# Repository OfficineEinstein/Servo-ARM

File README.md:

# Servo-ARM
Tester Controller per servo analogici (Futaba)
## Descrizione di massima
Questo dispoositivo nasce per consentire l'agevole studio dei generatori PWM, delle loro funzionalità e del loro sfruttamento. Per praticità è stato individuato come controllore per servo meccanismi a tre fili di tipo Futaba ma, in effetti è utilizzabile per un'ampio spettro di esperienze che comprendono l'utilizzo di segnali PWM o comunque la generazione di onde quadre o treni di impulsi anche associati ad un'uscita di potenza.

Il dispositivo si basa su 
##### * un microcontrollore Atmel ATMEGA328P installato su una scheda Arduino Nano equivalente.
##### * tre potenziometri per la scelta dell'ampiezza dell'inpulso dei 3 generatori PWM.
##### * quattro uscite per servo controllate tramite quattro semi ponti H.
##### * un alimentatore con ingresso in corrente continua o alternata e due unità di uscita separate (logica e servo).
Il potenziometro numero 3 è collegato a due uscite così da poter controllare due servo in contemporanea.

# Hardware
## r00
La versione zero (quella di cui attualmente sono disponibili i PCB) presenta alcune criticità in fase di correzione nella versione r01

### Ponnte raddrizzatore
Il ponte previsto nel PCB ha una piedinatura inusuale per cui, se si usa un ponte standard si devono piegare ed incrociare i piedini in maniera da posizion arli correttamente

### Piedinatura di uscita
La piedinatura di uscita per i servo ha i piedini 2 e 3 invertiti (fa riferimento ad un tipo di servo diverso dallo standard Futaba)

## r01
Nella versione r01 attualmente in fase di perfezionamento tutti i problemi evidenziati nella versione r00 sono in fase di eliminazione. I PCB della versione saranno facilemente riconoscibili anche attraverso la dicitura PCB r01 riportata nelle serigrafie

# Software
Al momento non è stata rilasciata una versione di riferimento del codice per il funzionamento di questo strumento.

Si ricorda che se si adotta come microcontrollore la scheda Maker Nano, in fase di compilazione si dovrà scegliere la versione di bootloader più aggiornata diversamente verrà restituito un errore in fase di caricamento del codice.

Il dispositivo si basa sulla funzione PWM disponibile nella libreria di base di Arduino (analogWrite()).
Anche se in fase di sperimentazione è possibile utilizzare le librerie disponibili per il controllo dei servo, sarebbe opportuno controllare i generatori PWM direttamente ovvero tramite comandi analogWrite() e non tramite chiamate alle librerie per il controllo dei servo.

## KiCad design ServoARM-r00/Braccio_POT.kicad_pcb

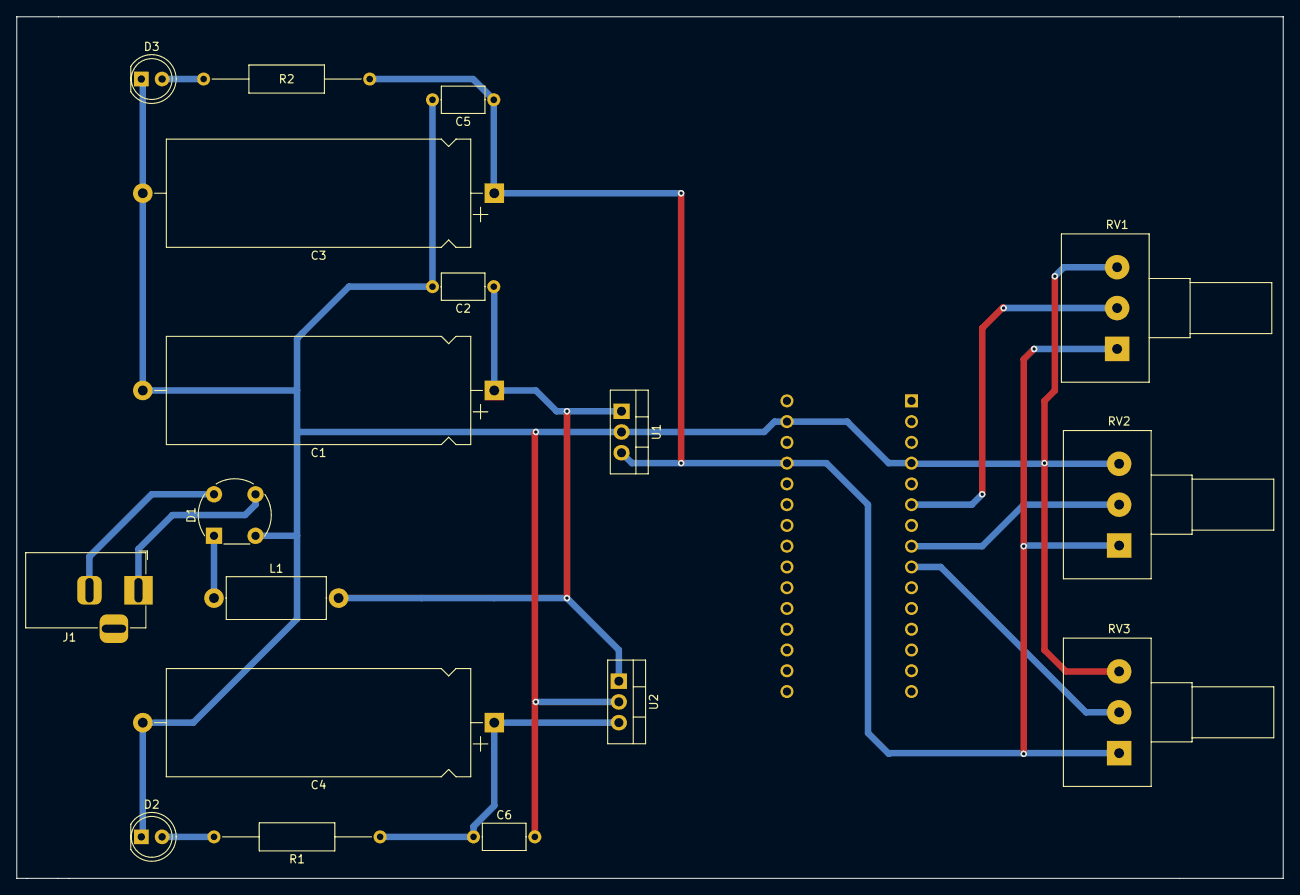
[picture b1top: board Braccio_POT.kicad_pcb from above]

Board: 2 copper layers, 154.9 x 105.4 mm, 19 parts (1 on the bottom side), 12 nets.

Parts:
A1: Arduino_Nano_v3.x; Arduino_Nano
C1, C3, C4: C_Polarized; CP_Axial_L37.0mm_D13.0mm_P43.00mm_Horizontal
C2, C5, C6: C; C_Axial_L5.1mm_D3.1mm_P7.50mm_Horizontal
D1: D_Bridge_+-AA; Diode_Bridge_Round_D8.9mm
D2: LED Verde; LED_D5.0mm
D3: LED Rosso; LED_D5.0mm
J1: Barrel_Jack_MountingPin; BarrelJack_Horizontal
L1: L; L_Axial_L12.0mm_D5.0mm_P15.24mm_Horizontal_Fastron_MISC
R1, R2: R; R_Axial_DIN0309_L9.0mm_D3.2mm_P20.32mm_Horizontal
RV1, RV2, RV3: R_Potentiometer; Potentiometer_Alps_RK163_Single_Horizontal
U1, U2: LM7805_TO220; TO-220-3_Vertical

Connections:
/Unità Alimentazione/5V-CPU: A1.27 (+5V), C3.1, C5.1, R2.1, RV1.1, RV2.1, RV3.1, U1.3 (VO)
/Unità Alimentazione/5V-SERVO: C4.1, C6.1, R1.1, U2.3 (VO)
/Unità Alimentazione/GND-Pow: A1.4 (GND), A1.29 (GND), C1.2, C2.2, C3.2, C4.2, C5.2, C6.2, D1.2 (-), D2.1 (K), D3.1 (K), RV1.3, RV2.3, RV3.3, U1.2 (GND), U2.2 (GND)
/Unità CPU/Pot1: A1.6 (D3), RV1.2
/Unità CPU/Pot2: A1.8 (D5), RV2.2
/Unità CPU/Pot3: A1.9 (D6), RV3.2
unnamed: C1.1, C2.1, L1.2, U1.1 (VI), U2.1 (VI)
unnamed: D1.1 (+), L1.1
unnamed: D1.3, J1.1
unnamed: D1.4, J1.2
unnamed: D2.2 (A), R1.2
unnamed: D3.2 (A), R2.2

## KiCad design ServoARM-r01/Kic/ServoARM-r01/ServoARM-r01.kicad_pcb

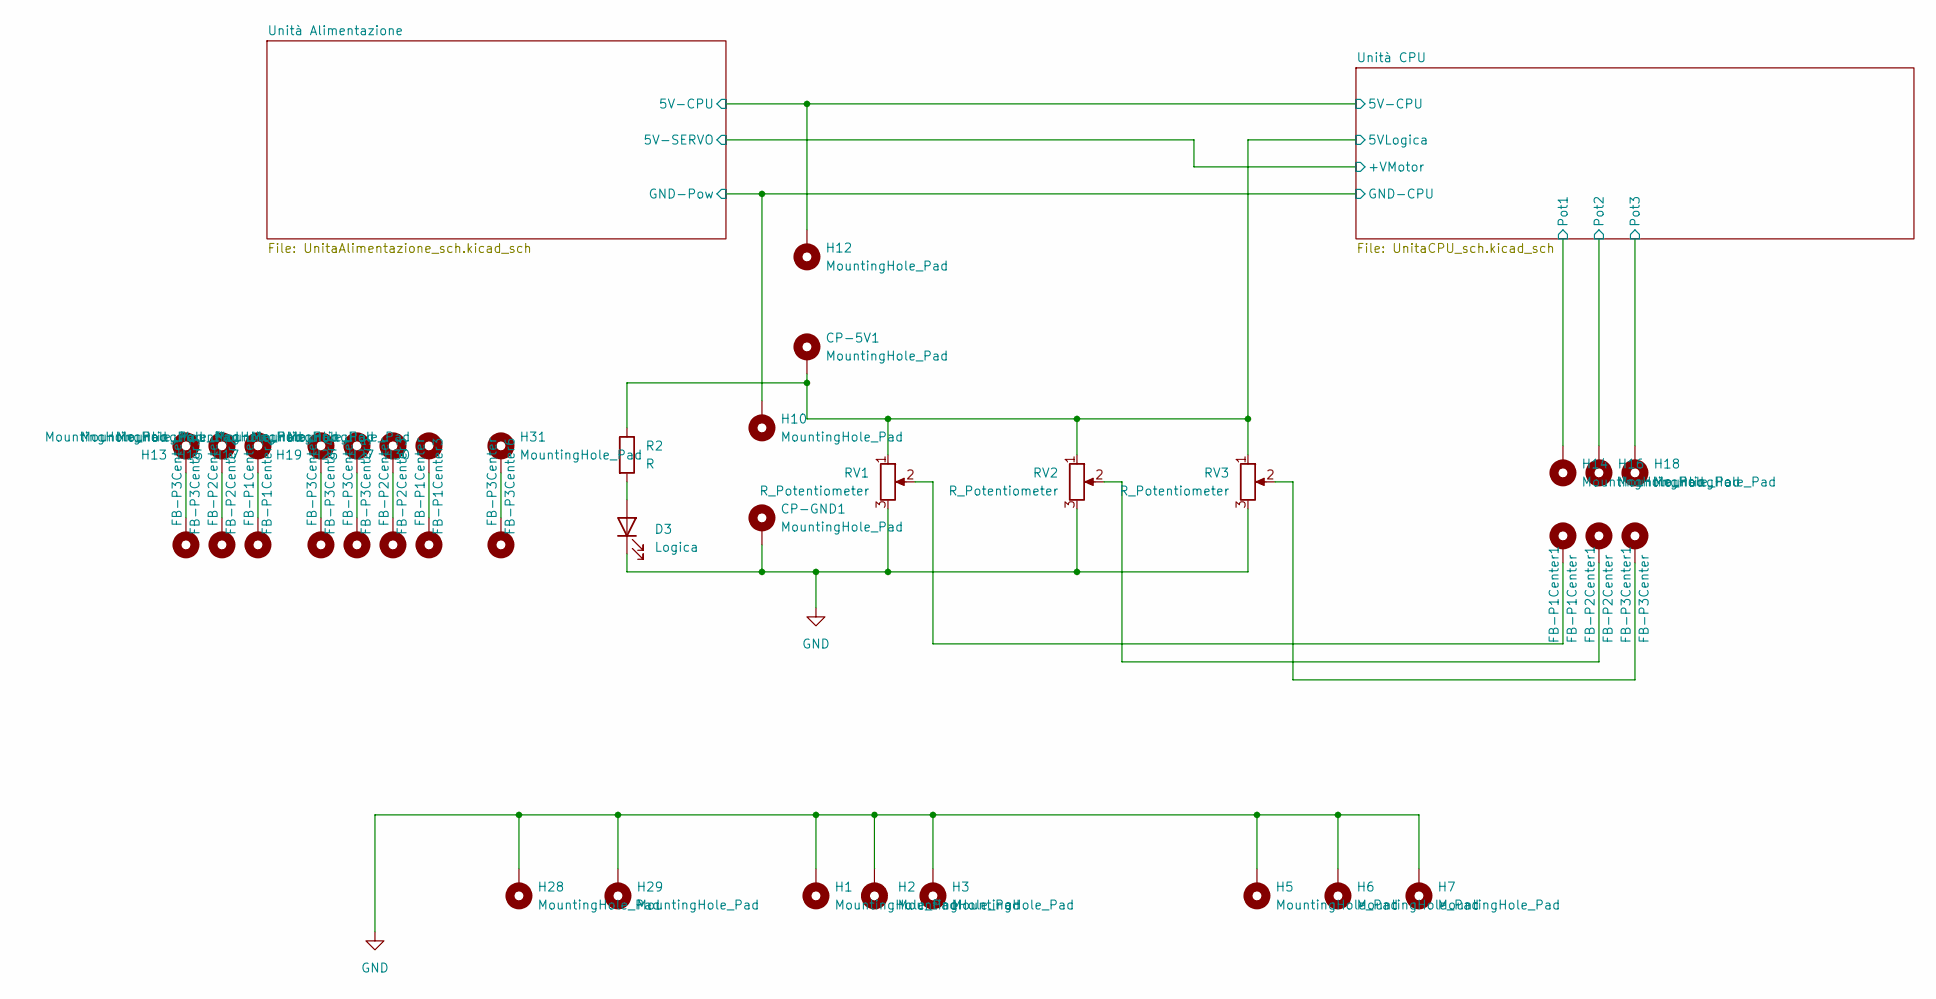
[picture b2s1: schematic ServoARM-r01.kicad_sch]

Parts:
CP-5V1: MountingHole_Pad; Asola
CP-GND1: MountingHole_Pad; Asola
D3: Logica; LED_D5.0mm
FB-P1Center1: FB-P1Center; Asola
FB-P1Center2, FB-P1Center3: FB-P1Center; TenonePerAsola
FB-P2Center1: FB-P2Center; Asola
FB-P2Center2, FB-P2Center3: FB-P2Center; TenonePerAsola
FB-P3Center1: FB-P3Center; Asola
FB-P3Center3, FB-P3Center4, FB-P3Center5, FB-P3Center6: FB-P3Center; TenonePerAsola
H1, H2: MountingHole_Pad; MountingHole_4.3x6.2mm_M4_Pad_Via
H3: MountingHole_Pad; MountingHole_4.3mm_M4_Pad_Via
H5, H6, H7, H28, H29: MountingHole_Pad; MountingHole_6.5mm_Pad_Via
H10, H12, H14, H16, H18: MountingHole_Pad; Asola
H13, H15, H17, H19, H25, H27, H30, H31: MountingHole_Pad; TenonePerAsola
R2: R; R_Axial_DIN0309_L9.0mm_D3.2mm_P20.32mm_Horizontal
RV1, RV2, RV3: R_Potentiometer; Potentiometer_Omeg_PC16BU_Vertical

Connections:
/Unità Alimentazione/5V-CPU: H12.1; also elsewhere on the board
/Unità CPU/5VLogica: CP-5V1.1, R2.1, RV1.1, RV2.1, RV3.1; also elsewhere on the board
/Unità CPU/Pot1: H14.1; also elsewhere on the board
/Unità CPU/Pot2: H16.1; also elsewhere on the board
/Unità CPU/Pot3: H18.1; also elsewhere on the board
GND: CP-GND1.1, D3.1 (K), H1.1, H2.1, H3.1, H5.1, H6.1, H7.1, H10.1, H28.1, H29.1, RV1.3, RV2.3, RV3.3; also elsewhere on the board
unnamed: D3.2 (A), R2.2
unnamed: FB-P1Center1.1, RV1.2
unnamed: FB-P1Center2.1, H17.1
unnamed: FB-P1Center3.1, H30.1
unnamed: FB-P2Center1.1, RV2.2
unnamed: FB-P2Center2.1, H15.1
unnamed: FB-P2Center3.1, H27.1
unnamed: FB-P3Center1.1, RV3.2
unnamed: FB-P3Center3.1, H13.1
unnamed: FB-P3Center4.1, H19.1
unnamed: FB-P3Center5.1, H25.1
unnamed: FB-P3Center6.1, H31.1

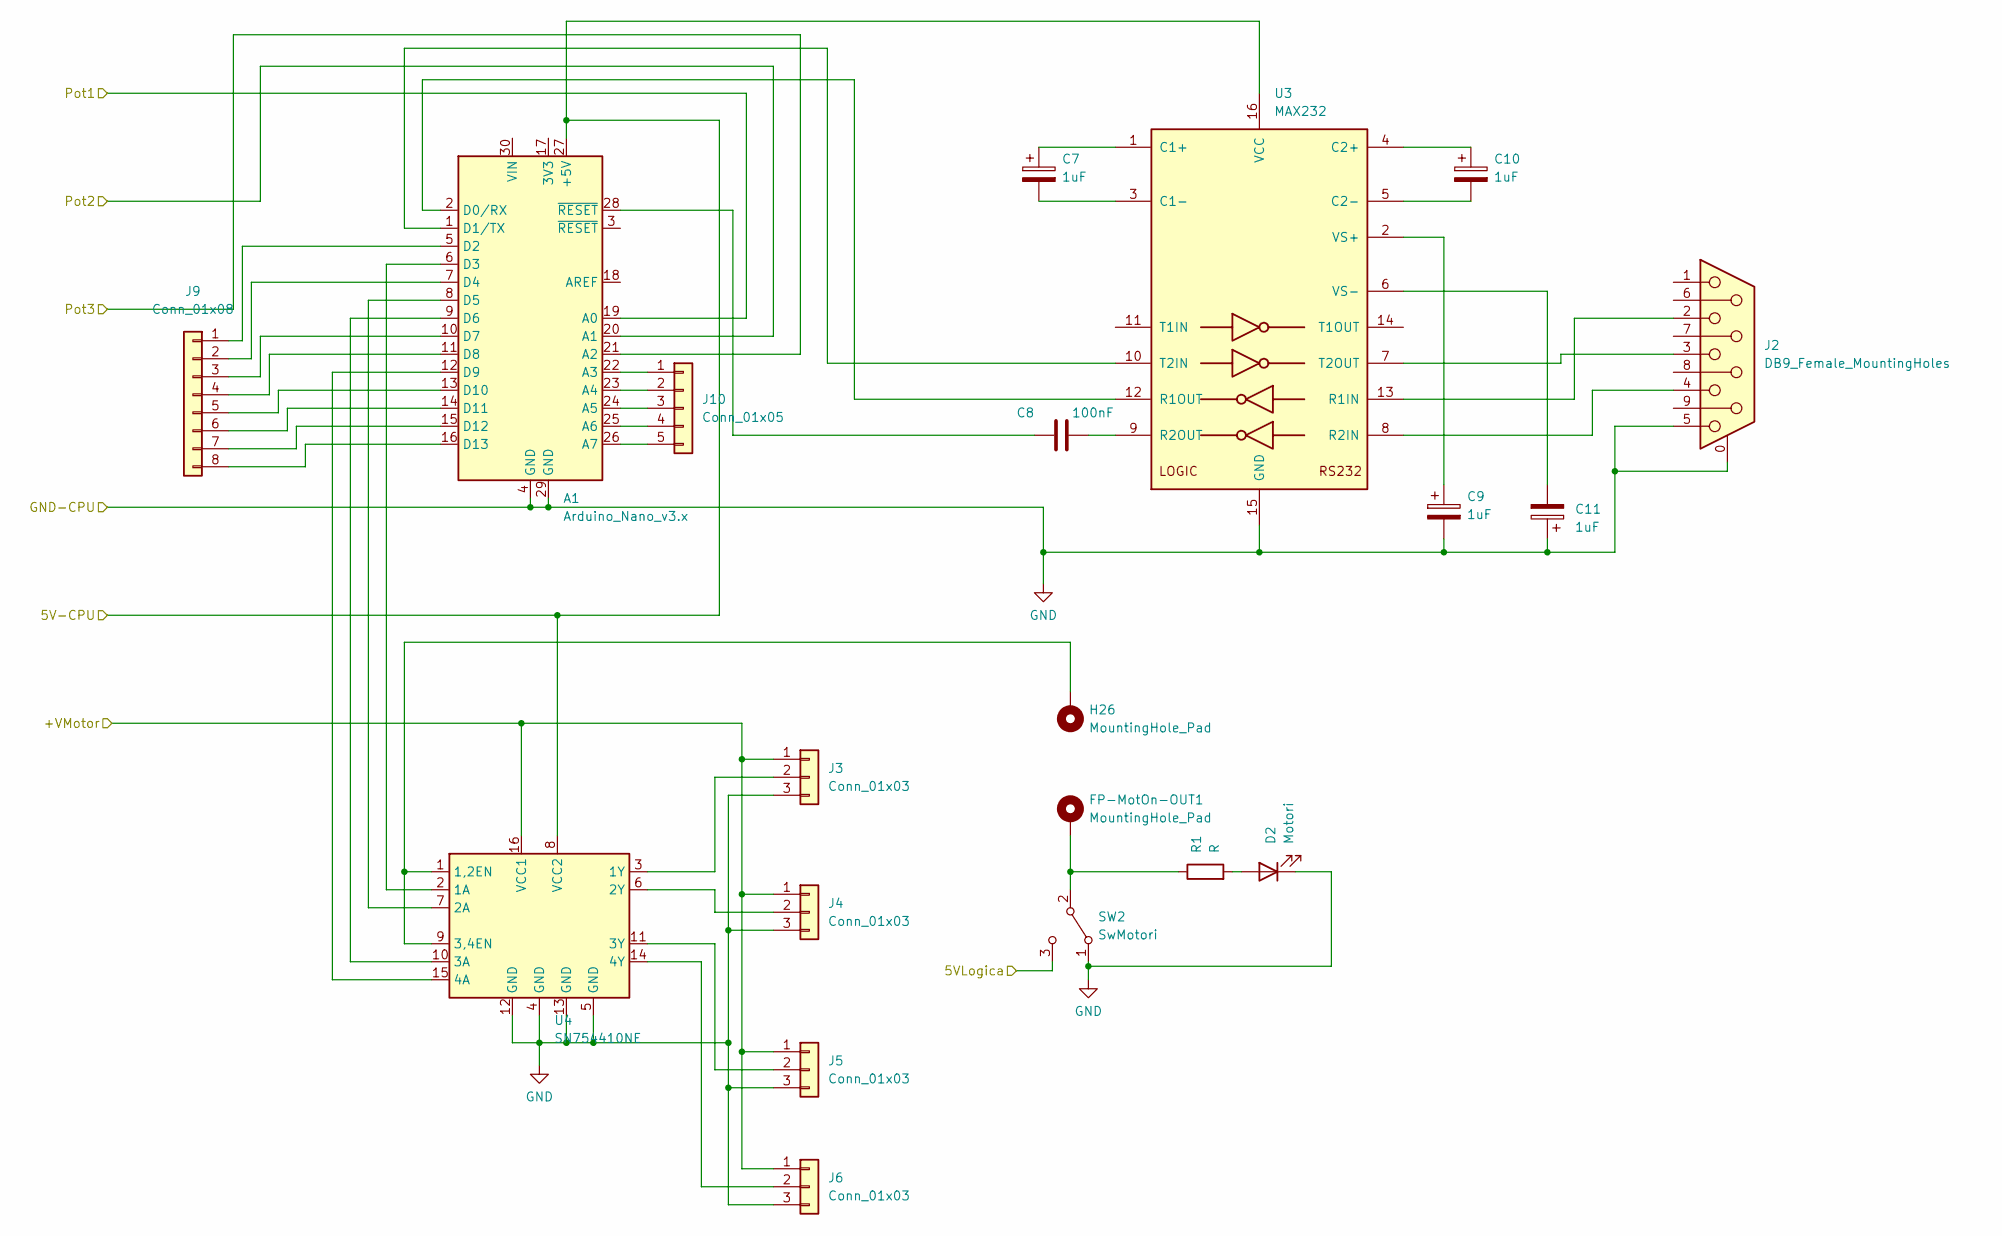
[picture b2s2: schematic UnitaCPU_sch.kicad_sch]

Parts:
A1: Arduino_Nano_v3.x; Arduino_Nano
C7, C9, C10, C11: 1uF; CP_Radial_D4.0mm_P2.00mm
C8: 100nF; C_Axial_L5.1mm_D3.1mm_P7.50mm_Horizontal
D2: Motori; LED_D5.0mm
FP-MotOn-OUT1: MountingHole_Pad; Asola
H26: MountingHole_Pad; Asola
J2: DB9_Female_MountingHoles; DSUB-9_Female_Horizontal_P2.77x2.84mm_EdgePinOffset14.56mm_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
J3, J4, J5, J6: Conn_01x03; PinHeader_1x03_P2.54mm_Horizontal
J9: Conn_01x08; PinHeader_1x08_P2.54mm_Vertical
J10: Conn_01x05; PinHeader_1x05_P2.54mm_Vertical
R1: R; R_Axial_DIN0309_L9.0mm_D3.2mm_P20.32mm_Horizontal
SW2: SwMotori; PinSocket_1x03_P2.54mm_Vertical
U3: MAX232; DIP-14_W7.62mm_LongPads
U4: SN754410NE; DIP-16_W7.62mm

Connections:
/Unità Alimentazione/5V-CPU: A1.27 (+5V), U3.16 (VCC), U4.8 (VCC2); also elsewhere on the board
/Unità Alimentazione/5V-SERVO: J3.1, J4.1, J5.1, J6.1, U4.16 (VCC1); also elsewhere on the board
/Unità CPU/5VLogica: SW2.3 (C); also elsewhere on the board
/Unità CPU/Pot1: A1.19 (A0); also elsewhere on the board
/Unità CPU/Pot2: A1.20 (A1); also elsewhere on the board
/Unità CPU/Pot3: A1.21 (A2); also elsewhere on the board
GND: A1.4 (GND), A1.29 (GND), C9.2, C11.1, D2.1 (K), J2.0 (PAD), J2.5, J3.3, J4.3, J5.3, J6.3, SW2.1 (A), U3.15 (GND), U4.4 (GND), U4.5 (GND), U4.12 (GND), U4.13 (GND); also elsewhere on the board
unnamed: A1.1 (D1/TX), U3.10 (T2IN)
unnamed: A1.2 (D0/RX), U3.12 (R1OUT)
unnamed: A1.5 (D2), J9.1
unnamed: A1.6 (D3), U4.2 (1A)
unnamed: A1.7 (D4), J9.2
unnamed: A1.8 (D5), U4.7 (2A)
unnamed: A1.9 (D6), U4.10 (3A)
unnamed: A1.10 (D7), J9.3
unnamed: A1.11 (D8), J9.4
unnamed: A1.12 (D9), U4.15 (4A)
unnamed: A1.13 (D10), J9.5
unnamed: A1.14 (D11), J9.6
unnamed: A1.15 (D12), J9.7
unnamed: A1.16 (D13), J9.8
unnamed: A1.22 (A3), J10.1
unnamed: A1.23 (A4), J10.2
unnamed: A1.24 (A5), J10.3
unnamed: A1.25 (A6), J10.4
unnamed: A1.26 (A7), J10.5
unnamed: A1.28 (~RESET), C8.1
unnamed: C7.1, U3.1 (C1+)
unnamed: C7.2, U3.3 (C1-)
unnamed: C8.2, U3.9 (R2OUT)
unnamed: C9.1, U3.2 (VS+)
unnamed: C10.1, U3.4 (C2+)
unnamed: C10.2, U3.5 (C2-)
unnamed: C11.2, U3.6 (VS-)
unnamed: D2.2 (A), R1.2
unnamed: FP-MotOn-OUT1.1, R1.1, SW2.2 (B)
unnamed: H26.1, U4.1 (1,2EN), U4.9 (3,4EN)
unnamed: J2.2, U3.13 (R1IN)
unnamed: J2.3, U3.7 (T2OUT)
unnamed: J2.4, U3.8 (R2IN)
unnamed: J3.2, U4.3 (1Y)
unnamed: J4.2, U4.6 (2Y)
unnamed: J5.2, U4.11 (3Y)
unnamed: J6.2, U4.14 (4Y)

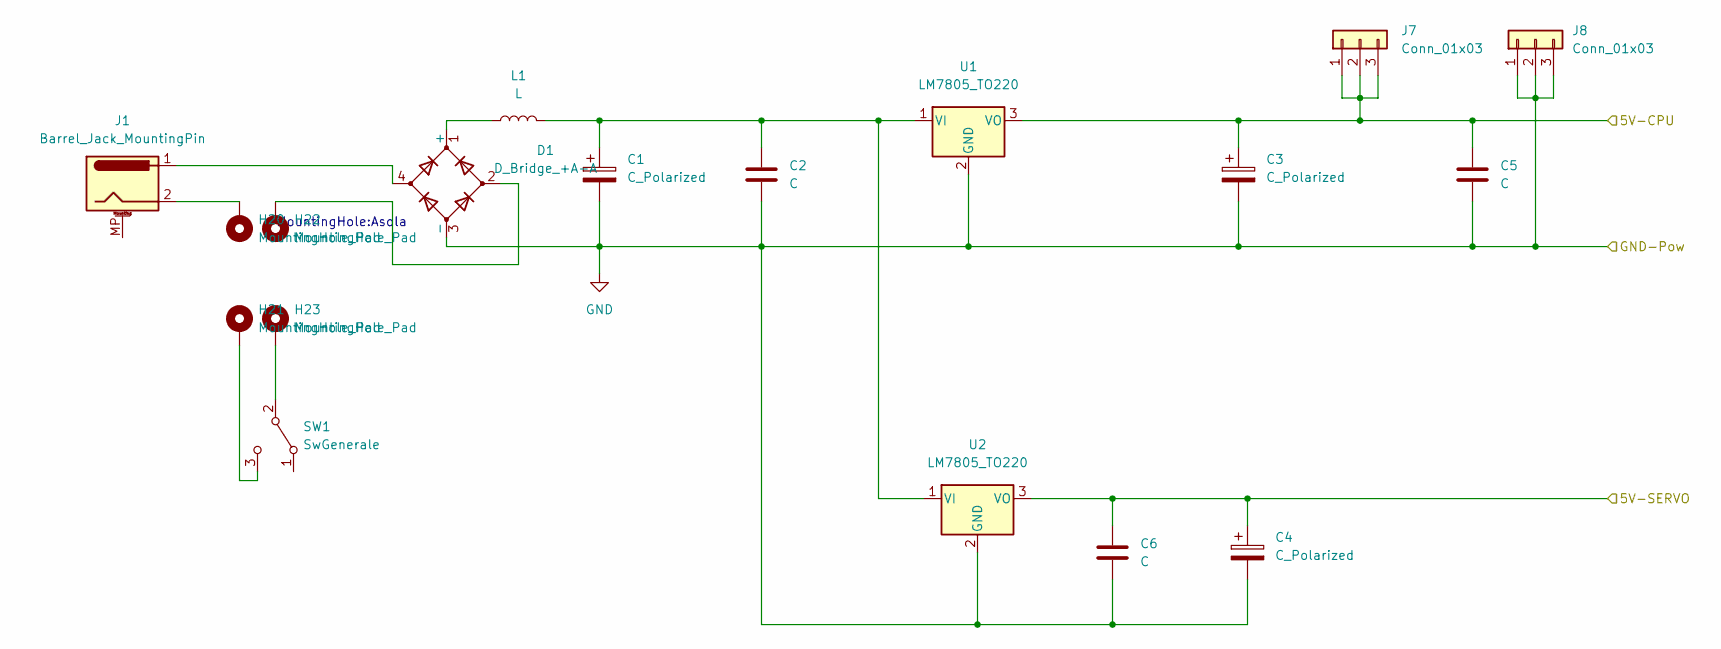
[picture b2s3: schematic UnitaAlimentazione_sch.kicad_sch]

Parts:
C1, C3, C4: C_Polarized; CP_Axial_L37.0mm_D13.0mm_P43.00mm_Horizontal
C2, C5, C6: C; C_Axial_L5.1mm_D3.1mm_P7.50mm_Horizontal
D1: D_Bridge_+A-A; Diode_Bridge_Round_D8.9mm
H20, H21, H22, H23: MountingHole_Pad; Asola
J1: Barrel_Jack_MountingPin; BarrelJack_Horizontal
J7, J8: Conn_01x03; PinHeader_1x03_P2.54mm_Vertical
L1: L; L_Axial_L12.0mm_D5.0mm_P15.24mm_Horizontal_Fastron_MISC
SW1: SwGenerale; PinSocket_1x03_P2.54mm_Vertical
U1, U2: LM7805_TO220; TO-220-3_Vertical

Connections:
/Unità Alimentazione/5V-CPU: C3.1, C5.1, J7.1, J7.2, J7.3, U1.3 (VO); also elsewhere on the board
/Unità Alimentazione/5V-SERVO: C4.1, C6.1, U2.3 (VO); also elsewhere on the board
GND: C1.2, C2.2, C3.2, C4.2, C5.2, C6.2, D1.3 (-), J8.1, J8.2, J8.3, U1.2 (GND), U2.2 (GND); also elsewhere on the board
unnamed: C1.1, C2.1, L1.2, U1.1 (VI), U2.1 (VI)
unnamed: D1.1 (+), L1.1
unnamed: D1.4, J1.1
unnamed: H20.1, J1.2
unnamed: H21.1, SW1.3 (C)
unnamed: D1.2, H22.1
unnamed: H23.1, SW1.2 (B)

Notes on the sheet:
MountingHole:Asola

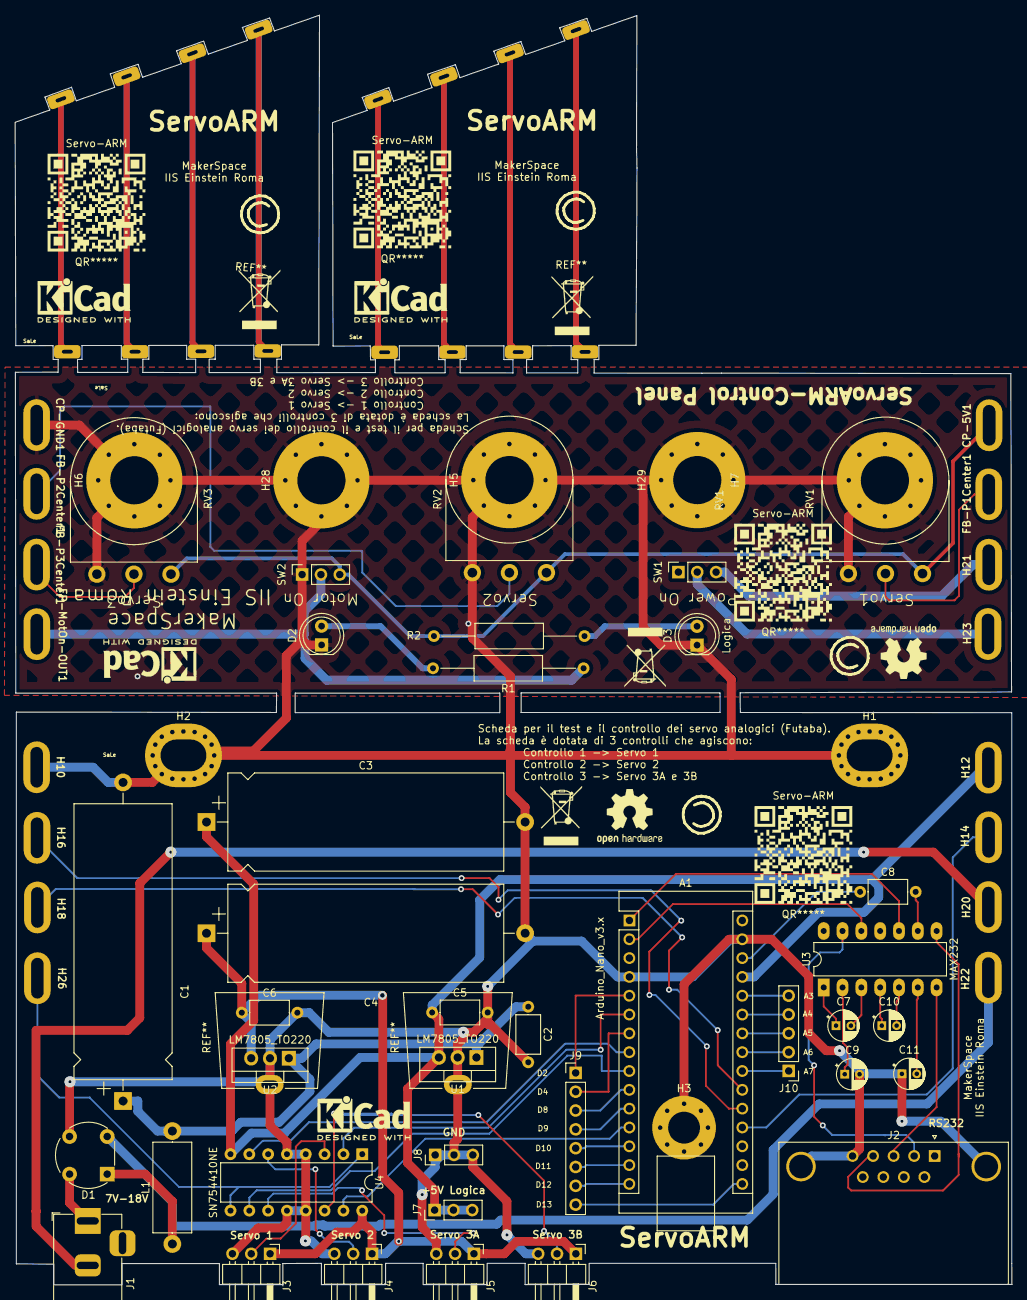
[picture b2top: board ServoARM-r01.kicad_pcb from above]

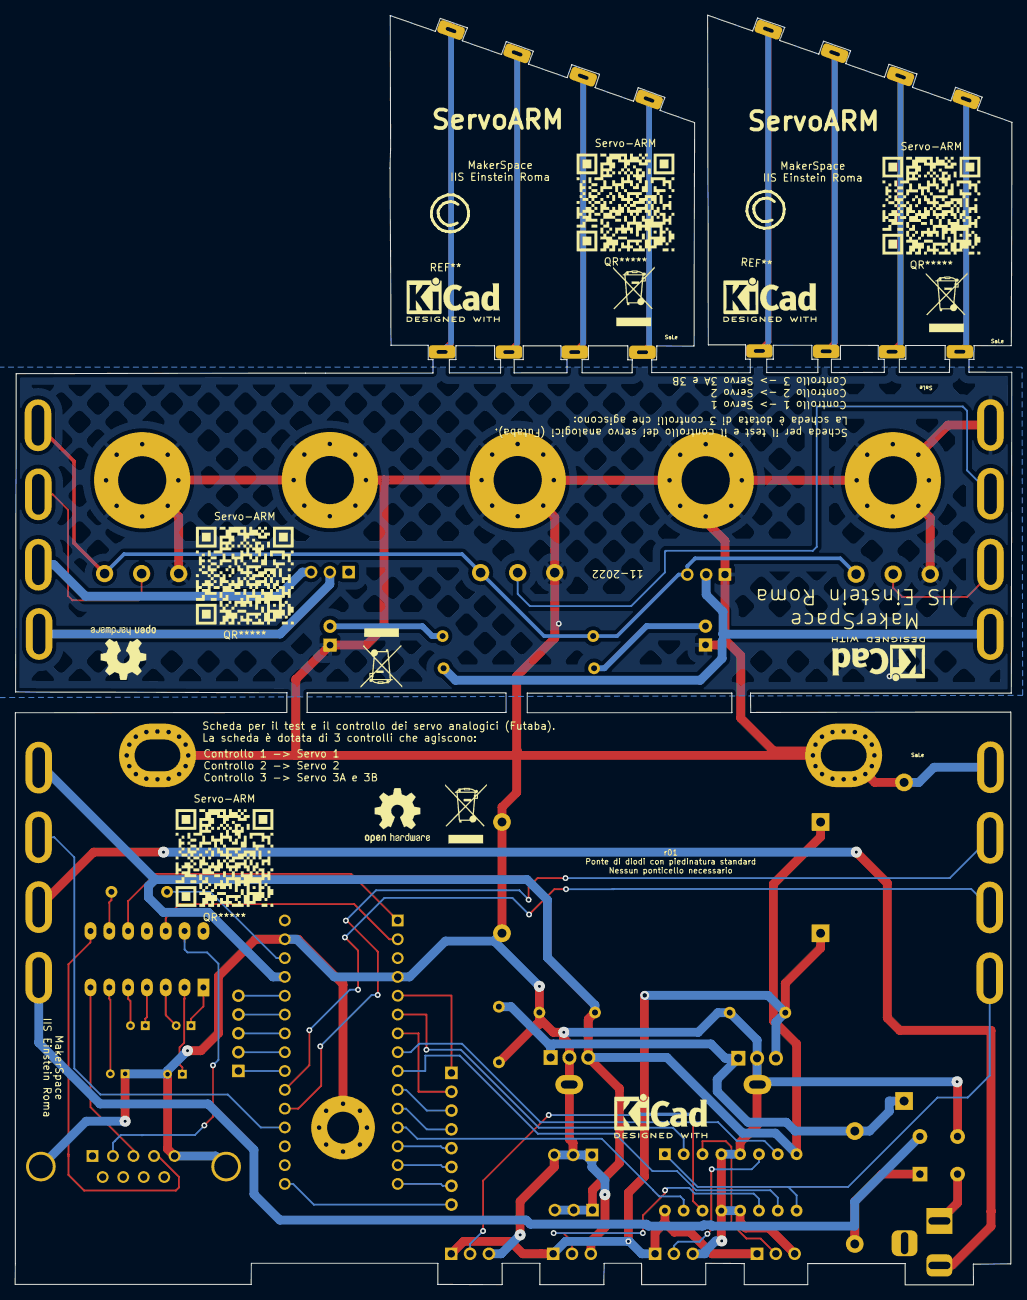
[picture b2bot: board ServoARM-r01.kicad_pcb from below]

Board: 2 copper layers, 134.5 x 171.3 mm, 85 parts (4 on the bottom side), 63 nets.

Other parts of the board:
QR*****: Servo-ARM
QR*****#2, QR*****#3, QR*****#4, QR*****#5, QR*****#6, QR*****#7, QR*****#8: Servo-ARM

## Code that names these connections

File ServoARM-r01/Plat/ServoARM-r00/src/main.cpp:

#include <Arduino.h>

//Gestione Potenziometri
#define NumPot 3
#define Pot1 0
#define Pot2 1
#define Pot3 2

uint8_t Pot[NumPot] = {Pot1, Pot2, Pot3};
uint16_t ARead[NumPot];

//Gestone ADC
#define ADCStep 1023

//Gestione PWM
#define PWMStep 255
#define NumPWMPort 4
#define PWMOut1 3
#define PWMOut2 5
#define PWMOut3 6
#define PWMOut4 9

uint8_t PWMOut[NumPWMPort] = {PWMOut1, PWMOut2, PWMOut3, PWMOut4};
uint16_t PWMVal[NumPWMPort];

void setup() 
{
  Serial.begin(115200);
  Serial.println("Prova Microfono");
}

void loop() 
{
  Serial.print("Potenziometro ");
  for (uint8_t ii=0; ii<NumPot; ii++)
  {
    Serial.print(ii+1);
    Serial.print(" -> ");
    //legge i singoli potenziometri (0-1023),
    //Carica il risultato nell'array ARead[] per successive elaborazioni
    ARead[ii] = analogRead(Pot[ii]);
    //Riproietta il valore letto dalla scala dell'ADC alla scala del PWM
    //e salva il valore per successive elaborazioni
    PWMVal[ii] = map(ARead[ii], 0, ADCStep, 0, PWMStep);
    Serial.print(PWMVal[ii]);
    Serial.print(" -");
    //Setta l'uscita corrispondente al potenziometro corrente
    //con il valore del PWM calcolato
    analogWrite(PWMOut[ii],PWMVal[ii]);
    //Se è il terzo potenziometro setta la quarta uscita allo stesso valore
    if (ii==2)
    {
      ii++;
      analogWrite(PWMOut[ii],PWMVal[ii-1]);
    }
  }
  Serial.println();
  delay(20);
}

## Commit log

2022-11-09 Add files via upload
    VErsione priva di valori per i componenti passivi
2022-12-19 Add files via upload
    Aggiornata alimentazione ponte H
